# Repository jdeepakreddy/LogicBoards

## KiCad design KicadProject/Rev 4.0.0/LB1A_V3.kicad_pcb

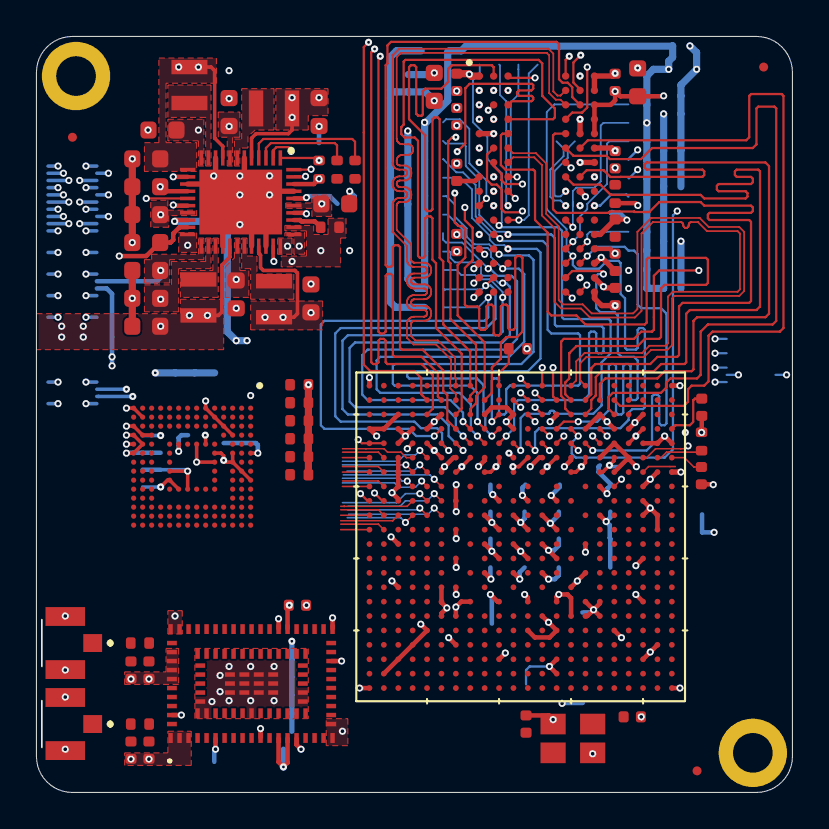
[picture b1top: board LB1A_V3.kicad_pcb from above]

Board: 6 copper layers, 42.0 x 42.0 mm, 187 parts (0 on the bottom side), 284 nets.

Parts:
C101, C105: 10nF; C_0402_1005Metric
C102, C103, C104: 10pF; C_0402_1005Metric
C201, C202, C203, C205, C206, C207, C208, C209, C210, C211, C212, C213, C214, C215, C216, C217, C218, C220, C221, C225, C226, C227, C228, C317, C325, C336, C337, C501, C502, C503, C504, C601, C607, C609: 100nF; C_0402_1005Metric
C223, C224, C401, C402, C403, C404, C405, C406, C407, C408, C412, C413, C414, C415, C416, C417: 10uF; C_0603_1608Metric
C229, C230, C409, C418, C419, C420, C421: 22uF; C_0603_1608Metric
C301, C302, C303, C304, C305, C306, C307, C308, C309, C310, C311, C312, C313, C314, C315, C316, C321, C322, C323, C324, C326, C327, C328, C329, C330, C331, C332, C333, C334, C335, C338, C339, C340, C342: 1uF; C_0402_1005Metric
C410, C505, C506, C507, C606, C608: 4.7uF; C_0402_1005Metric
C411: 1uF; C_0603_1608Metric
C508: 2.2uF; C_0402_1005Metric
C602, C603, C604, C605: DNF; C_0402_1005Metric
FID701, FID702, FID703, FID704, FID705, FID706: Fiducial; Fiducial_0.5mm_Mask1.5mm
H701, H702: MountingHole_Pad; MountingHole_2.2mm_M2_DIN965_Pad
J601, J602: 2337019-1; 23370191
L401, L402, L403, L404: 1uH; MGV2520101R0M-10
R101: 3k; R_0402_1005Metric
R104, R105: 1k5; R_0402_1005Metric
R106, R221, R222, R501, R502, R503, R504, R505, R506, R507, R508, R509, R510, R603, R604, R605, R606, R607: 10k; R_0402_1005Metric
R201, R210: 240E; R_0402_1005Metric
R202, R203, R204, R205, R206, R207, R208, R209, R211, R212, R213, R214, R215, R216, R217, R218, R219, R220, R223, R224, R225, R227, R228, R229: 56E; R_0402_1005Metric
R226: 100E; R_0402_1005Metric
R301, R608: DNF; R_0402_1005Metric
R302, R401, R402, R601, R602: 0E; R_0402_1005Metric
U101: STM32MP157CAA3
U201: AS4C256M16D3LC-12BCN
U401: STPMIC1xPQR; STPMIC1BPQR
U501: S40FC004C1B2C00000
U601: LBEE59B1LV-278; LBEE59B1LV278
U701: DF40C-70DP-0.4V(51); DF40C70DP04V51
U702, U703: DF40C-100DP-0.4V(51); DF40C100DP04V51
X101: 32.768kHz; SiT1533AC-H5-DCC-32.768E
Y101: 24MHz; TSX3225240000MF10ZC3

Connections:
5V_VIN: C401.1, C402.1, C403.1, C404.1, C406.1, C407.1, C408.1, R401.2, R402.2, U401.8, U401.12, U401.19, U401.22, U401.24, U401.28, U401.36, U702.83, U702.84, U702.85, U702.86, U702.89, U702.90, U702.91, U702.92, U702.95, U702.96, U702.97, U702.98
/HSE_IN: C102.2, U101.T1, Y101.1
/HSE_OUT: C103.2, U101.T2, Y101.3
/LSE_IN: C104.1, U101.P1, X101.3
/MPU_DDR3L_Memory/DDR_A0: R202.2, U101.K19, U201.N3
/MPU_DDR3L_Memory/DDR_A1: R203.2, U101.M18, U201.P7
/MPU_DDR3L_Memory/DDR_A2: R204.2, U101.J18, U201.P3
/MPU_DDR3L_Memory/DDR_A3: R205.2, U101.J19, U201.N2
/MPU_DDR3L_Memory/DDR_A4: R206.2, U101.T18, U201.P8
/MPU_DDR3L_Memory/DDR_A5: R207.2, U101.H19, U201.P2
/MPU_DDR3L_Memory/DDR_A6: R208.2, U101.U19, U201.R8
/MPU_DDR3L_Memory/DDR_A7: R209.2, U101.F18, U201.R2
/MPU_DDR3L_Memory/DDR_A8: R211.2, U101.U18, U201.T8
/MPU_DDR3L_Memory/DDR_A9: R212.2, U101.H18, U201.R3
/MPU_DDR3L_Memory/DDR_A10: R213.2, U101.N18, U201.L7
/MPU_DDR3L_Memory/DDR_A11: R214.2, U101.P19, U201.R7
/MPU_DDR3L_Memory/DDR_A12: R215.2, U101.N19, U201.N7
/MPU_DDR3L_Memory/DDR_A13: R216.2, U101.G18, U201.T3
/MPU_DDR3L_Memory/DDR_A14: R217.2, U101.P18, U201.T7
/MPU_DDR3L_Memory/DDR_BA0: R218.2, U101.K20, U201.M2
/MPU_DDR3L_Memory/DDR_BA1: R219.2, U101.R18, U201.N8
/MPU_DDR3L_Memory/DDR_BA2: R220.2, U101.K18, U201.M3
/MPU_DDR3L_Memory/DDR_CASN: R225.2, U101.M22, U201.K3
/MPU_DDR3L_Memory/DDR_CKE: R222.2, R227.2, U101.R19, U201.K9
/MPU_DDR3L_Memory/DDR_CLK_N: R226.1, U101.N21, U201.K7
/MPU_DDR3L_Memory/DDR_CLK_P: R226.2, U101.N20, U201.J7
/MPU_DDR3L_Memory/DDR_CSN: R228.2, U101.L18, U201.L2
/MPU_DDR3L_Memory/DDR_DQ0: U101.E21, U201.D7
/MPU_DDR3L_Memory/DDR_DQ1: U101.F21, U201.A7
/MPU_DDR3L_Memory/DDR_DQ2: U101.H21, U201.A3
/MPU_DDR3L_Memory/DDR_DQ3: U101.E20, U201.B8
/MPU_DDR3L_Memory/DDR_DQ4: U101.J21, U201.C2
/MPU_DDR3L_Memory/DDR_DQ5: U101.H20, U201.C3
/MPU_DDR3L_Memory/DDR_DQ6: U101.H22, U201.A2
/MPU_DDR3L_Memory/DDR_DQ7: U101.G19, U201.C8
/MPU_DDR3L_Memory/DDR_DQ8: U101.N22, U201.F2
/MPU_DDR3L_Memory/DDR_DQ9: U101.R21, U201.E3
/MPU_DDR3L_Memory/DDR_DQ10: U101.P21, U201.G2
/MPU_DDR3L_Memory/DDR_DQ11: U101.T20, U201.H7
/MPU_DDR3L_Memory/DDR_DQ12: U101.V20, U201.F7
/MPU_DDR3L_Memory/DDR_DQ13: U101.R20, U201.H3
/MPU_DDR3L_Memory/DDR_DQ14: U101.U21, U201.H8
/MPU_DDR3L_Memory/DDR_DQ15: U101.V21, U201.F8
/MPU_DDR3L_Memory/DDR_DQM0: U101.G20, U201.D3
/MPU_DDR3L_Memory/DDR_DQM1: U101.T21, U201.E7
/MPU_DDR3L_Memory/DDR_DQS0_N: U101.G21, U201.B7
/MPU_DDR3L_Memory/DDR_DQS0_P: U101.G22, U201.C7
/MPU_DDR3L_Memory/DDR_DQS1_N: U101.R22, U201.G3
/MPU_DDR3L_Memory/DDR_DQS1_P: U101.T22, U201.F3
/MPU_DDR3L_Memory/DDR_ODT: R224.2, U101.L21, U201.K1
/MPU_DDR3L_Memory/DDR_RASN: R223.2, U101.M20, U201.J3
/MPU_DDR3L_Memory/DDR_RESETN: R221.2, U101.F19, U201.T2
/MPU_DDR3L_Memory/DDR_WEN: R229.2, U101.M21, U201.L3
ANA0: U101.R4, U703.84
ANA1: U101.T5, U703.83
BOOT0: U101.N3, U703.32
BOOT1: U101.N4, U703.33
BOOT2: U101.P4, U703.34
BT_DEV_WAKE: U101.H3, U601.29
BT_HOST_WAKE: U101.A2, U601.5
BT_PCM_CLK: U101.G2, U601.85
BT_PCM_SDI: U101.H5, U601.82
BT_PCM_SDO: U101.K5, U601.84
BT_PCM_WS: U101.F4, U601.83
BT_REG_ON: U101.G3, U601.9
BT_RF_OUT: C602.1, R601.2, U601.49
BT_USART3_CTS: U101.W1, U601.33
BT_USART3_RTS: U101.W12, U601.34
BT_USART3_RX: U101.AA7, U601.31
BT_USART3_TX: U101.V9, U601.32
DSI_CK_N: U101.A16, U703.95
DSI_CK_P: U101.B16, U703.96
DSI_D0_N: U101.A15, U703.99
DSI_D0_P: U101.B15, U703.100
DSI_D1_N: U101.A17, U703.97
DSI_D1_P: U101.B17, U703.98
GND: C101.2, C102.1, C103.1, C104.2, C105.2, C201.2, C202.2, C203.2, C205.2, C206.2, C207.2, C208.2, C209.2, C210.2, C211.2, C212.2, C213.2, C214.2, C215.2, C216.2, C217.2, C218.2, C220.2, C221.2, C223.2, C224.2, C225.2, C226.2, C227.2, C228.2, C229.2, C230.2, C301.2, C302.2, C303.2, C304.2, C305.2, C306.2, C307.2, C308.2, C309.2, C310.2, C311.2, C312.2, C313.2, C314.2, C315.2, C316.2, C317.2, C321.2, C322.2, C323.2, C324.2, C325.1, C326.2, C327.2, C328.2, C329.2, C330.2, C331.2, C332.2, C333.2, C334.2, C335.2, C336.2, C337.2, C338.2, C339.2, C340.2, C342.2, C401.2, C402.2, C403.2, C404.2, C405.2, C406.2, C407.2, C408.2, C409.1, C410.2, C411.1, C412.1, C413.1, C414.1, C415.1, C416.1, C417.1, C418.2, C419.2, C420.2, C421.2, C501.2, C502.2, C503.2, C504.2, C505.2, C506.2, C507.2, C508.2, C601.2, C602.2, C603.2, C604.2, C605.2, C606.2, C607.2, C608.2, C609.2, H701.1, H702.1, J601.2, J601.3, J602.2, J602.3, R101.2, R201.2, R210.2, R221.1, R222.1, U101.A1, U101.A19, U101.A22, U101.AA4, U101.AA12, U101.AA13, U101.AA16, U101.AA18, U101.AB1, U101.AB18, U101.AB22, U101.B2, U101.B19, U101.C3, U101.C8, U101.C11, U101.C14, U101.C15, U101.C16, U101.C17, U101.C18, U101.C19, U101.C20, U101.D4, U101.D19, U101.E5, U101.E19, U101.F6, U101.F7, U101.F8, U101.F16, U101.F20, U101.G4, U101.G6, U101.G8, U101.G10, U101.G12, U101.G14, U101.G17, U101.H7, U101.J9, U101.J11, U101.J13, U101.J17, U101.J20, U101.K3, U101.K7, U101.K10, U101.K12, U101.K14, U101.L9, U101.L11, U101.L13, U101.L17, U101.L19, U101.L20, U101.M5, U101.M7, U101.M10, U101.M12, U101.M14, U101.N6, U101.N9, U101.N11, U101.N13, U101.N17, U101.P2, U101.P3, U101.P5, U101.P7, U101.P10, U101.P12, U101.P14, U101.P20, U101.R6, U101.R8, U101.R17, U101.T6, U101.T7, U101.T9, U101.T11, U101.T19, U101.U6, U101.U7, U101.U13, U101.U15, U101.U17, U101.U20, U101.V5, U101.V16, U101.V18, U101.V19, U101.W17, U101.W19, U101.Y3, U101.Y7, U101.Y10, U101.Y13, U101.Y14, U101.Y15, U101.Y18, U101.Y20, U201.A9, U201.B1, U201.B3, U201.B9, U201.D1, U201.D8, U201.E1, U201.E2, U201.E8, U201.F9, U201.G1, U201.G8, U201.G9, U201.J2, U201.J8, U201.M1, U201.M9, U201.P1, U201.P9, U201.T1, U201.T9, U401.6, U401.10, U401.15, U401.26, U401.30, U401.32, U401.41, U401.ep, U501.A6, U501.C4, U501.D3, U501.E2, U501.E7, U501.F1, U501.G5, U501.H10, U501.J5, U501.K8, U501.N2, U501.N5, U501.P1, U501.P4, U501.P6, U601.1, U601.2, U601.3, U601.6, U601.11, U601.15, U601.19, U601.20, U601.27, U601.30, U601.36, U601.47, U601.48, U601.50, U601.51, U601.52, U601.53, U601.57, U601.59, U601.60, U601.65, U601.72, U601.73, U601.94, U601.95, U601.96, U601.97, U601.98, U601.99, U601.100, U601.101, U601.102, U601.103, U601.104, U601.105, U601.106, U701.37, U701.39, U701.41, U701.43, U701.47, U701.49, U701.51, U701.53, U701.63, U701.65, U702.33, U702.34, U702.39, U702.40, U702.57, U702.58, U702.63, U702.64, U702.69, U702.70, U702.75, U702.76, U702.81, U702.82, U702.87, U702.88, U702.93, U702.94, U702.99, U702.100, U703.45, U703.47, U703.57, U703.59, X101.2, Y101.2, Y101.4
I2C4_SCL: R104.1, U101.G1, U401.4, U703.86
I2C4_SDA: R105.1, U101.H4, U401.3, U703.85
JTDI: U101.D16, U701.33
JTDO_TRACESWO: U101.E16, U701.42
JTRST: U101.E15, U701.35
LPO_32: U101.AB10, U601.80
MPU_VDDA_1V8_REG: C335.1, C336.1, U101.AB12, U101.B14
NRST: C101.1, R106.1, U101.R2, U401.1, U501.J1, U501.J2, U501.J3, U501.K5, U703.82
unnamed: C105.1, U101.R1
unnamed: C317.1, R301.1, R302.1, U101.M4
unnamed: C330.1, U101.AB17
unnamed: C342.1, U101.A18, U101.B18
unnamed: C409.2, U401.34
unnamed: C410.1, U401.40
unnamed: C508.1, U501.C1, U501.C2
unnamed: C603.1, J601.1, R601.1
unnamed: C604.1, R602.2, U601.58
unnamed: C605.1, J602.1, R602.1
unnamed: L401.1, U401.7
unnamed: L402.1, U401.11
unnamed: L403.1, U401.29
unnamed: L404.1, U401.25
unnamed: R101.1, U101.AA17
unnamed: R201.1, U201.L8
unnamed: R210.1, U101.K22
unnamed: R401.1, U401.33
unnamed: R402.1, U401.37
OTG_VBUS: U101.V15, U701.24
PA0_WAKEUP: U101.AA3, U401.43
PA1: U101.V4, U701.1
PA2: U101.AB2, U701.2
PA3: U101.T4, U701.3
PA4: U101.V6, U701.4
PA5: U101.U5, U701.5
PA6: U101.W9, U701.6
PA7: U101.Y9, U701.7
PA10: U101.Y17, U701.8
PA11: U101.Y16, U701.9
PA12: U101.W16, U701.10
PA13: U101.W3, U701.11
PA14: U101.R3, U701.12
PA15: U101.E11, U701.13
PB0: U101.AB5, U701.14
PB1: U101.AA5, U701.15
PB2: U101.V13, U701.16
PB5: U101.AA8, U701.17
PB6: U101.W13, U701.18
PB7: U101.F11, U701.19
PB8: U101.AB8, U701.20
PB9: U101.F12, U701.21
PB11: U101.Y5, U701.22
PB13: U101.V10, U701.23
PC0: U101.U10, U701.70
PC1: U101.AB3, U701.69
PC2: U101.Y1, U701.68
PC3: U101.U3, U701.67
PC4: U101.AB6, U701.66
PC5: U101.AA6, U701.40
PC6: U101.E13, U701.64
PC7: U101.D13, U701.34
PD0: U101.C10, U701.57
PD1: U101.B10, U701.56
PD4: U101.C9, U701.54
PD5: U101.A9, U701.32
PD6: U101.L3, U701.52
PD8: U101.M1, U701.29
PD9: U101.M2, U701.50
PD10: U101.A8, U701.30
PD11: U101.AB9, U701.48
PD13: U101.V14, U701.31
PD14: U101.M3, U701.46
PE0: U101.C5, U702.1
PE1: U101.D7, U702.2
PE2: U101.Y2, U702.3
PE4: U101.F15, U702.4
PE6: U101.E9, U702.5
PE7: U101.W10, U702.6
PE8: U101.Y12, U702.7
PE9: U101.W11, U702.8
PE10: U101.W14, U702.9
PE11: U101.D5, U702.10
PE12: U101.E4, U702.11
PE13: U101.A4, U702.12
PE14: U101.B4, U702.13
PE15: U101.C4, U702.14
PF2: U101.F13, U702.15
PF3: U101.V3, U702.16
PF6: U101.AA11, U702.17
PF7: U101.AA10, U702.18
PF9: U101.AB11, U702.19
PF10: U101.V12, U702.20
PF11: U101.W8, U702.21
PF12: U101.V8, U702.22
PF13: U101.W7, U702.23
PF14: U101.V7, U702.24
PF15: U101.W6, U702.25
PG0: U101.W5, U703.80
PG1: U101.Y4, U703.70
PG2: U101.W4, U703.79
PG3: U101.U4, U703.69
PG4: U101.AB4, U703.78
PG5: U101.U8, U703.68
PG7: U101.Y11, U703.77
PG8: U101.Y8, U703.67
PG9: U101.W15, U703.76
PG10: U101.AA9, U703.66
PG11: U101.U11, U703.75
PG12: U101.J4, U703.65
PG13: U101.AA1, U703.74
PG14: U101.AA2, U703.64
PH2: U101.AB7, U703.73
PH3: U101.Y6, U703.56
PH6: U101.V11, U703.72
PH7: U101.W2, U703.63
PH8: U101.D6, U703.71
PH9: U101.E6, U703.55
PH10: U101.B1, U703.62
PH11: U101.B3, U703.61
PH12: U101.F5, U703.60
PH13: U101.D3, U703.54
PH14: U101.C2, U703.58
PH15: U101.C1, U703.53
PI0: U101.D1, U703.1
PI1: U101.E2, U703.2
PI2: U101.E1, U703.3
PI3: U101.E3, U703.4
PI4: U101.J6, U703.5
PI5: U101.F2, U703.6
PI6: U101.G5, U703.7
PI7: U101.F1, U703.8
PI8: U101.N1, U703.9
PI9: U101.J5, U703.10
PI11: U101.T3, U703.11
PI12: U101.H2, U703.12
PI13: U101.H1, U703.13
PI14: U101.D2, U703.14
PI15: U101.F3, U703.15
PJ0: U101.J2, U703.16
PJ1: U101.L6, U703.17
PJ2: U101.K4, U703.18
PJ3: U101.J1, U703.19
PJ4: U101.K2, U703.20
PJ5: U101.K1, U703.21
PJ6: U101.L5, U703.22
PJ7: U101.H6, U703.23
PJ8: U101.L4, U703.24
PJ9: U101.J3, U703.25
PJ10: U101.L2, U703.26
PJ11: U101.K6, U703.27
PJ12: U101.B8, U703.28
PJ13: U101.A7, U703.29
PJ14: U101.B7, U703.30
PJ15: U101.C7, U703.31
PK0: U101.D8, U703.94
PK1: U101.E7, U703.93
PK2: U101.E8, U703.92
PK3: U101.B6, U703.91
PK4: U101.A6, U703.90
PK5: U101.C6, U703.89
PK6: U101.A5, U703.88
PK7: U101.B5, U703.87
PMIC_LDO1_1V8: C413.2, C606.1, C607.1, C608.1, C609.1, R603.1, R604.1, R605.1, R606.1, R607.1, R608.1, U401.23, U601.13, U601.14, U601.35, U702.65, U702.66, U702.67, U702.68
PMIC_LDO2_2V9: C415.2, U401.18, U702.77, U702.78, U702.79, U702.80
PMIC_LDO3_VTT_DDR: C203.1, C205.1, C206.1, C208.1, C209.1, C210.1, C211.1, C225.1, C226.1, C227.1, C228.1, C229.1, C230.1, C412.2, R202.1, R203.1, R204.1, R205.1, R206.1, R207.1, R208.1, R209.1, R211.1, R212.1, R213.1, R214.1, R215.1, R216.1, R217.1, R218.1, R219.1, R220.1, R223.1, R224.1, R225.1, R227.1, R228.1, R229.1, U401.14
PMIC_LDO4_VDD_USB: C337.1, C417.2, U101.AB13, U101.AB16, U401.39
PMIC_LDO5_2V9: C416.2, C501.1, C502.1, C503.1, C504.1, C505.1, C506.1, C507.1, R501.1, R502.1, R503.1, R504.1, R505.1, R506.1, R507.1, R508.1, R509.1, R510.1, U401.20, U501.A9, U501.B8, U501.C6, U501.C7, U501.E6, U501.F5, U501.J10, U501.K9, U501.M4, U501.N4, U501.P3, U501.P5, U702.35, U702.36, U702.37, U702.38
PMIC_LDO6_1V0: C414.2, U401.21, U702.71, U702.72, U702.73, U702.74
PMIC_VOUT1_VDD_CORE: C305.1, C306.1, C307.1, C308.1, C313.1, C314.1, C315.1, C316.1, C321.1, C322.1, C323.1, C324.1, C326.1, C327.1, C328.1, C329.1, C418.1, L401.2, U101.H9, U101.H11, U101.H13, U101.H15, U101.J8, U101.J10, U101.J12, U101.J14, U101.K9, U101.K11, U101.K13, U101.K15, U101.L8, U101.L10, U101.L12, U101.L14, U101.M11, U101.M13, U101.M15, U101.N12, U101.N14, U101.P13, U101.P15, U101.R14, U101.T15, U401.5
PMIC_VOUT2_VDD_DDR: C212.1, C213.1, C214.1, C215.1, C216.1, C217.1, C218.1, C220.1, C221.1, C223.1, C224.1, C331.1, C332.1, C333.1, C334.1, C338.1, C339.1, C340.1, C405.1, C419.1, L402.2, U101.E18, U101.F17, U101.G16, U101.H17, U101.J16, U101.K17, U101.L16, U101.M17, U101.N16, U101.P17, U101.R16, U101.T17, U101.U16, U101.V17, U101.W18, U101.Y19, U201.A1, U201.A8, U201.B2, U201.C1, U201.C9, U201.D2, U201.D9, U201.E9, U201.F1, U201.G7, U201.H2, U201.H9, U201.K2, U201.K8, U201.N1, U201.N9, U201.R1, U201.R9, U401.9, U401.13
PMIC_VOUT3_VDD: C301.1, C302.1, C303.1, C304.1, C309.1, C310.1, C311.1, C312.1, C420.1, L403.2, R104.2, R105.2, R106.2, R302.2, U101.A14, U101.D18, U101.M6, U101.M9, U101.N5, U101.N8, U101.N10, U101.P9, U101.P11, U101.R5, U101.R10, U101.R12, U101.T13, U101.U2, U101.U9, U101.U12, U101.U14, U101.V2, U401.31, U401.42, X101.4
PMIC_VOUT4_3V3: C421.1, L404.2, U401.27, U702.51, U702.52, U702.53, U702.54, U702.55, U702.56, U702.59, U702.60, U702.61, U702.62
PMIC_VREF_DDR: C201.1, C202.1, C207.1, C411.2, U101.AB19, U201.H1, U201.M8, U401.16
PMIC_WAKEUP: U101.N2, U401.2
PONKEYn: U401.17, U703.81
POWER_ON: U101.V1, U401.44
SDMMC1_CK: U101.E12, U701.58
SDMMC1_CMD: U101.D12, U701.55
SDMMC1_D0: U101.E14, U701.62
SDMMC1_D1: U101.D14, U701.61
SDMMC1_D2: U101.F14, U701.60
SDMMC1_D3: U101.D15, U701.59
SDMMC2_CK: R509.2, U101.A10, U501.K1, U501.K2, U501.K3, U501.M6
SDMMC2_CMD: R510.2, U101.D11, U501.L1, U501.L2, U501.L3, U501.M5
SDMMC2_D0: R501.2, U101.A13, U501.A3
SDMMC2_D1: R502.2, U101.B12, U501.A4
SDMMC2_D2: R503.2, U101.A12, U501.A5
SDMMC2_D3: R504.2, U101.C13, U501.A1, U501.B2
SDMMC2_D4: R505.2, U101.B13, U501.A2, U501.B3
SDMMC2_D5: R506.2, U101.A11, U501.B4, U501.C3, U501.D2, U501.E1
SDMMC2_D6: R507.2, U101.C12, U501.B5, U501.C5, U501.D4, U501.E3, U501.F2, U501.G1
SDMMC2_D7: R508.2, U101.B11, U501.A8, U501.B6, U501.B7
SDMMC3_CK: R606.2, U101.D10, U601.24
SDMMC3_CMD: R608.2, U101.B9, U601.26
SDMMC3_D0: R605.2, U101.E10, U601.23
SDMMC3_D1: R604.2, U101.F9, U601.22
SDMMC3_D2: R603.2, U101.D9, U601.21
SDMMC3_D3: R607.2, U101.F10, U601.25
STLINK_SWCLK: U101.D17, U701.44
STLINK_SWDIO: U101.E17, U701.45
USB1_N: U101.AB15, U701.25
USB1_P: U101.AA15, U701.26
USB2_N: U101.AA14, U701.27
USB2_P: U101.AB14, U701.28
VDDA: C325.2, U101.P6
VDDOUT_VDDIO: C601.1, U601.4, U601.28
WL_HOST_WAKE: U101.L1, U601.7
WL_REG_ON: U101.A3, U601.10

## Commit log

2021-08-30 Added Rev 4.0.0
2021-08-30 updated board size to 43x43
2021-08-30 Cleared all traces for rerouting.
2021-08-30 updated connectors coutyards
2021-08-30 working on ground connections
2021-08-30 updated courtyards of connectors
2021-08-30 updated drill holes positions
2021-08-30 PCB resized to 42x42
2021-08-30 adjusted connector location
2021-08-30 Passives adjustments
2021-08-30 working on grounds
2021-08-30 working on mpu grounds
2021-08-30 still working on mpu grounds
2021-08-30 mpu grounding complete
2021-08-30 clock grounding complete
2021-08-30 Ground connections complete
2021-08-31 working on PMIC power
2021-08-31 working on power
2021-08-31 power routing
2021-09-02 working on power planes
2021-09-02 5v power plane
2021-09-02 power planes
2021-09-02 L3 polygon complete
2021-09-02 ram power routing
2021-09-02 power planes complete.
2021-09-02 started ddr3 routing
2021-09-02 working on ddr3 routing
2021-09-02 routed another ddr3 track
2021-09-02 rerouting ddr3 tracks
2021-09-02 ddr3 clk routed
2021-09-02 DQM0_routed
2021-09-02 somemore routing
2021-09-02 routing ram
2021-09-02 lunch break
2021-09-02 another trace
2021-09-02 some more traces
2021-09-02 Updated ram routes
2021-09-02 differential clock in ram routed
2021-09-02 one more trace left
2021-09-02 one trace left
2021-09-02 top plane all ddr3 traces completed
2021-09-03 working on bottom layer ddr traces
2021-09-03 working on l6 ddr routing
2021-09-03 couple of couple routes
2021-09-03 couple of traces
2021-09-03 couple of more traces
2021-09-03 updated polygon pours
2021-09-03 couple more traces
2021-09-03 adjustments to traces
2021-09-03 some more traces left
2021-09-04 cleaning traces on L6 and rerouting
2021-09-04 some more changes
2021-09-04 adjusted ground via
2021-09-04 routed some traces
2021-09-04 some more traces done
2021-09-04 ram complete. Pull up resistors pending
2021-09-04 pull up resistors left
2021-09-06 address line pullup resistors
2021-09-06 working on ram
2021-09-06 ram little more left
2021-09-06 some more routing
2021-09-08 added altium project
2021-09-08 library additions
2021-09-08 added symbols to library
2021-09-08 Converted SchLib and PCBLib to Integrated Library
2021-09-08 modified sch page template
2021-09-09 Working on MPU IO schematic
2021-09-09 WORKING ON SCH
2021-09-11 project commmit
2021-09-11 Added components to library
2021-09-11 added symbols to lib and updated sch
2021-09-11 Updated schematic
2021-09-11 UPDATED SCH
2021-09-11 MODIFIED SCH
2021-09-13 ADDED LIB SYMBOLS

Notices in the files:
parts and their libraries:
Copyright 2021 Accelerated Designs. All rights reserved.
